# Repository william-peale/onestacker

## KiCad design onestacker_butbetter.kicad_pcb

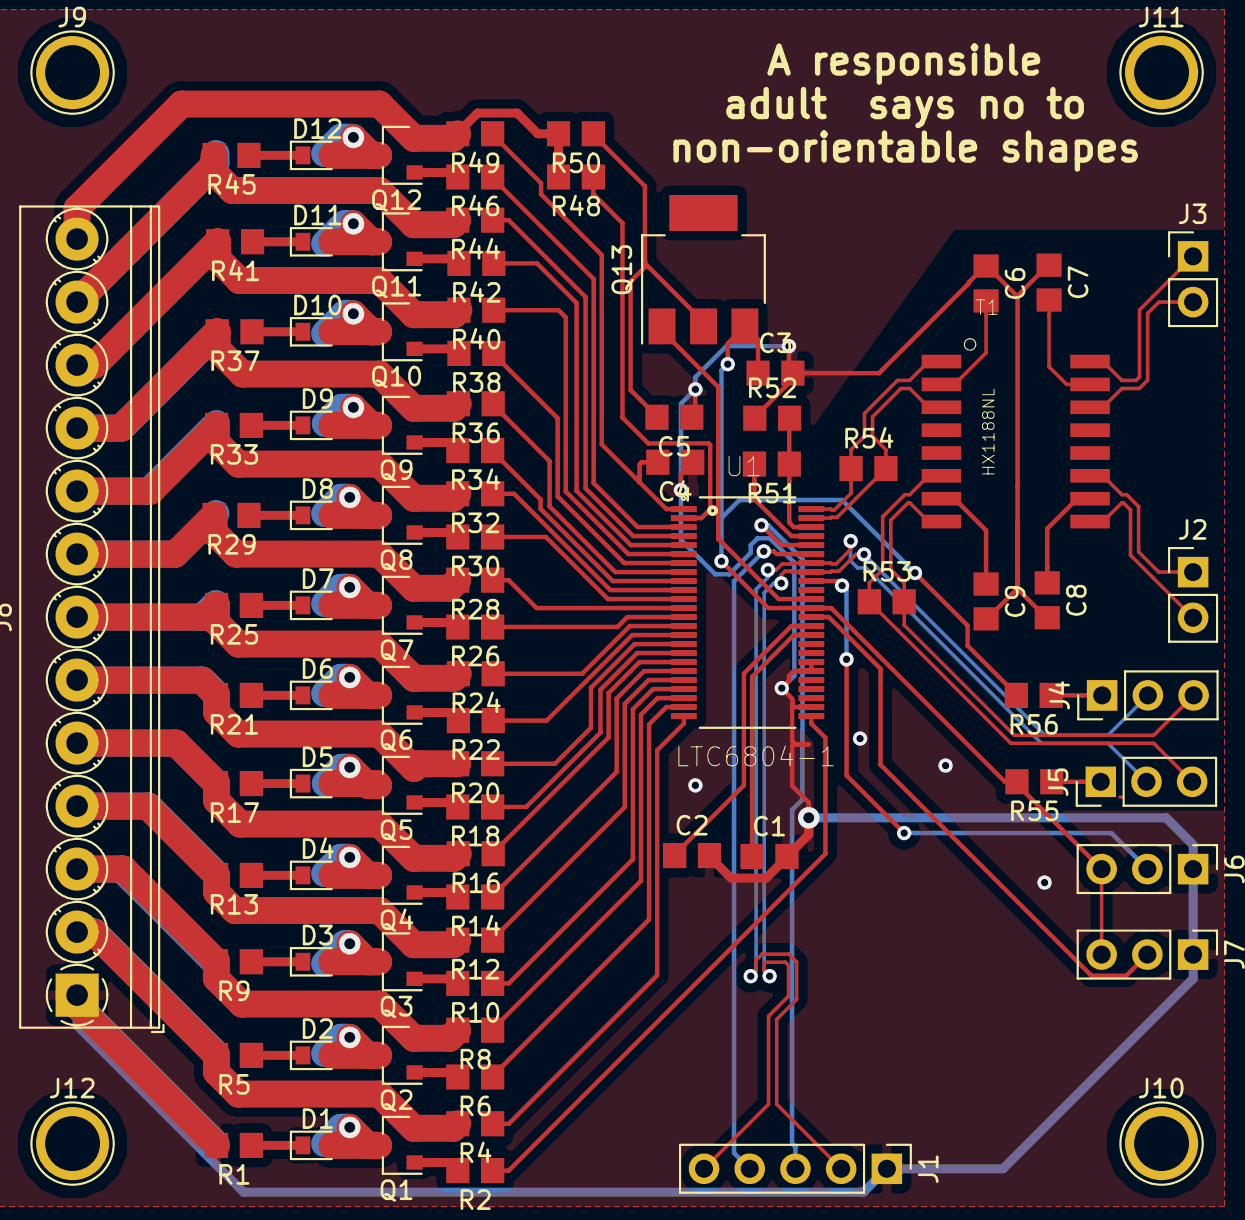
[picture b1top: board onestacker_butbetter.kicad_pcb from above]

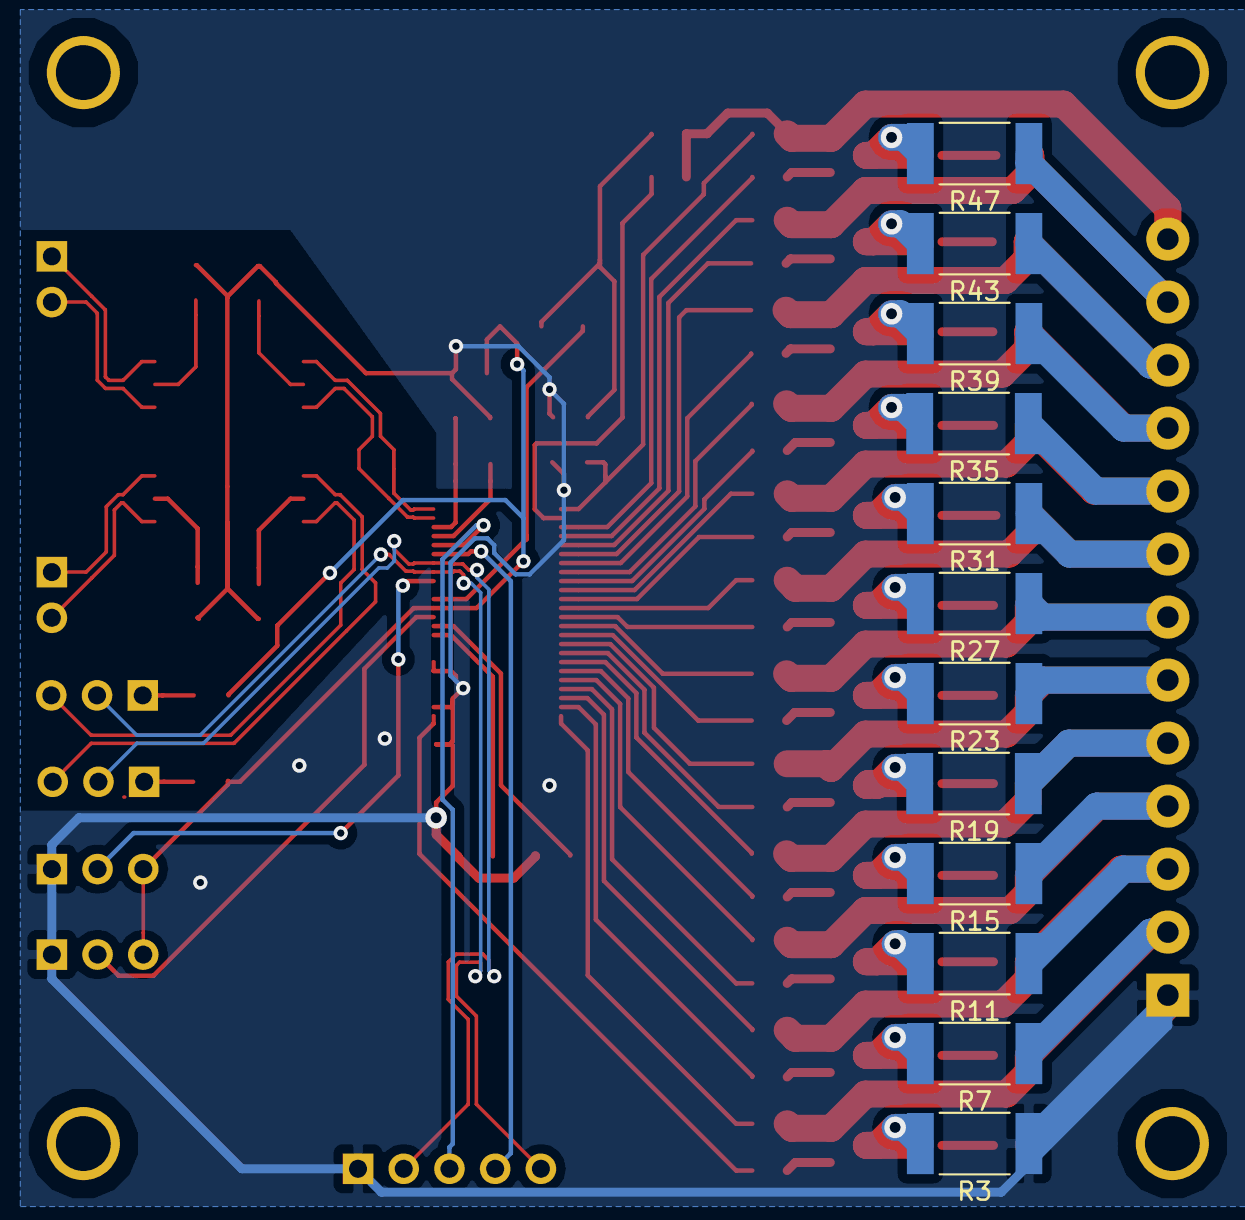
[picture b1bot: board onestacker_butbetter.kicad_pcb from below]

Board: 2 copper layers, 104 parts (12 on the bottom side), 101 nets.

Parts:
C1, C2, C3: 1uf; C_0805_2012Metric_Pad1.29x1.40mm_HandSolder
C4, C5: 0.1uf; C_0805_2012Metric_Pad1.29x1.40mm_HandSolder
C6, C7, C8, C9: 51pf; C_0805_2012Metric_Pad1.29x1.40mm_HandSolder
D1, D2, D3, D4, D5, D6, D7, D8, D9, D10, D11, D12: LED_Small; LED_0603_1608Metric_Pad0.82x1.00mm_HandSolder
J1: Conn_01x05; PinHeader_1x05_P2.54mm_Vertical
J2, J3: Conn_01x02; PinHeader_1x02_P2.54mm_Vertical
J4, J5, J6, J7: Conn_01x03; PinHeader_1x03_P2.54mm_Vertical
J8: Conn_01x13; TerminalBlock_Phoenix_PT-1,5-13-3.5-H_1x13_P3.50mm_Horizont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
J9, J10, J11, J12: Conn_01x01; 1pin
Q1, Q2, Q3, Q4, Q5, Q6, Q7, Q8, Q9, Q10, Q11, Q12: BSS138; SOT-23
Q13: NSV1C201MZ4; SOT-223
R1, R5, R9, R13, R17, R21, R25, R29, R33, R37, R41, R45: 110R; R_0805_2012Metric_Pad1.29x1.40mm_HandSolder
R2, R6, R10, R14, R18, R22, R26, R30, R34, R38, R42, R46: 3.3k; R_0805_2012Metric_Pad1.29x1.40mm_HandSolder
R3, R7, R11, R15, R19, R23, R27, R31, R35, R39, R43, R47: 16.5R; R_2512_6332Metric_Pad1.49x3.40mm_HandSolder
R4, R8, R12, R16, R20, R24, R28, R32, R36, R40, R44, R48, R49, R50: 100R; R_0805_2012Metric_Pad1.29x1.40mm_HandSolder
R51: 806R; R_0805_2012Metric_Pad1.29x1.40mm_HandSolder
R52: 1.2k; R_0805_2012Metric_Pad1.29x1.40mm_HandSolder
R53, R54: 120R; R_0805_2012Metric_Pad1.29x1.40mm_HandSolder
R55, R56: 1M; R_0805_2012Metric_Pad1.29x1.40mm_HandSolder
T1: HX1188NL; HXXXX
U1: LTC6804-1; SOP50P780X200-48N

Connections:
/IA2_N: J4.3, R53.2, T1.8
/IA2_P: J5.3, R53.1, T1.6
/OA_N: J3.2, T1.14
/OA_P: J3.1, T1.16
/OB_N: J2.2, T1.9
/OB_P: J2.1, T1.11
GND: C1.2, C2.2, C3.2, C4.1, C5.1, C6.1, C7.1, C8.2, C9.2, J1.1, J6.1, J7.1, J8.1, R1.2, R3.1, R52.1, U1.26, U1.30, U1.31
IA_N: J1.5, J4.2, U1.41
IA_P: J1.2, J5.2, U1.42
IB_N: R54.2, T1.3, U1.47
IB_P: R54.1, T1.1, U1.48
ISOMOD: J6.2, U1.40
unnamed: C1.1, U1.34
unnamed: C2.1, U1.35
unnamed: C4.2, R49.1, U1.1
unnamed: C5.2, Q13.2, R50.1
unnamed: C6.2, T1.2
unnamed: C7.2, T1.15
unnamed: C8.1, T1.10
unnamed: C9.1, T1.7
unnamed: D1.1, R1.1
unnamed: D1.2, Q1.3, R3.2
unnamed: D2.1, R5.1
unnamed: D2.2, Q2.3, R7.2
unnamed: D3.1, R9.1
unnamed: D3.2, Q3.3, R11.2
unnamed: D4.1, R13.1
unnamed: D4.2, Q4.3, R15.2
unnamed: D5.1, R17.1
unnamed: D5.2, Q5.3, R19.2
unnamed: D6.1, R21.1
unnamed: D6.2, Q6.3, R23.2
unnamed: D7.1, R25.1
unnamed: D7.2, Q7.3, R27.2
unnamed: D8.1, R29.1
unnamed: D8.2, Q8.3, R31.2
unnamed: D9.1, R33.1
unnamed: D9.2, Q9.3, R35.2
unnamed: D10.1, R37.1
unnamed: D10.2, Q10.3, R39.2
unnamed: D11.1, R41.1
unnamed: D11.2, Q11.3, R43.2
unnamed: D12.1, R45.1
unnamed: D12.2, Q12.3, R47.2
unnamed: J1.3, U1.44
unnamed: J1.4, U1.43
unnamed: J4.1, R56.1
unnamed: J5.1, R55.1
unnamed: J8.2, Q1.2, R4.2, R5.2, R7.1
unnamed: J8.3, Q2.2, R8.2, R9.2, R11.1
unnamed: J8.4, Q3.2, R12.2, R13.2, R15.1
unnamed: J8.5, Q4.2, R16.2, R17.2, R19.1
unnamed: J8.6, Q5.2, R20.2, R21.2, R23.1
unnamed: J8.7, Q6.2, R24.2, R25.2, R27.1
unnamed: J8.8, Q7.2, R28.2, R29.2, R31.1
unnamed: J8.9, Q8.2, R32.2, R33.2, R35.1
unnamed: J8.10, Q9.2, R36.2, R37.2, R39.1
unnamed: J8.11, Q10.2, R40.2, R41.2, R43.1
unnamed: J8.12, Q11.2, R44.2, R45.2, R47.1
unnamed: J8.13, Q12.2, R48.2, R49.2, R50.2
unnamed: Q1.1, R2.2
unnamed: Q2.1, R6.2
unnamed: Q3.1, R10.2
unnamed: Q4.1, R14.2
unnamed: Q5.1, R18.2
unnamed: Q6.1, R22.2
unnamed: Q7.1, R26.2
unnamed: Q8.1, R30.2
unnamed: Q9.1, R34.2
unnamed: Q10.1, R38.2
unnamed: Q11.1, R42.2
unnamed: Q12.1, R46.2
unnamed: Q13.1, U1.38
unnamed: R2.1, U1.25
unnamed: R4.1, U1.24
unnamed: R6.1, U1.23
unnamed: R8.1, U1.22
unnamed: R10.1, U1.21
unnamed: R12.1, U1.20
unnamed: R14.1, U1.19
unnamed: R16.1, U1.18
unnamed: R18.1, U1.17
unnamed: R20.1, U1.16
unnamed: R22.1, U1.15
unnamed: R24.1, U1.14
unnamed: R26.1, U1.13
unnamed: R28.1, U1.12
unnamed: R30.1, U1.11
unnamed: R32.1, U1.10
unnamed: R34.1, U1.9
unnamed: R36.1, U1.8
unnamed: R38.1, U1.7
unnamed: R40.1, U1.6
unnamed: R42.1, U1.5
unnamed: R44.1, U1.4
unnamed: R46.1, U1.3
unnamed: R48.1, U1.2
unnamed: R51.1, R52.2, U1.46
unnamed: R51.2, U1.45
SWTEN: J7.2, U1.36
VDD: C3.1, J6.3, J7.3, Q13.3, R55.2, R56.2, U1.37

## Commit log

2018-08-05 kicad cooler
2018-08-15 cool69
2018-08-15 fixed package issue
